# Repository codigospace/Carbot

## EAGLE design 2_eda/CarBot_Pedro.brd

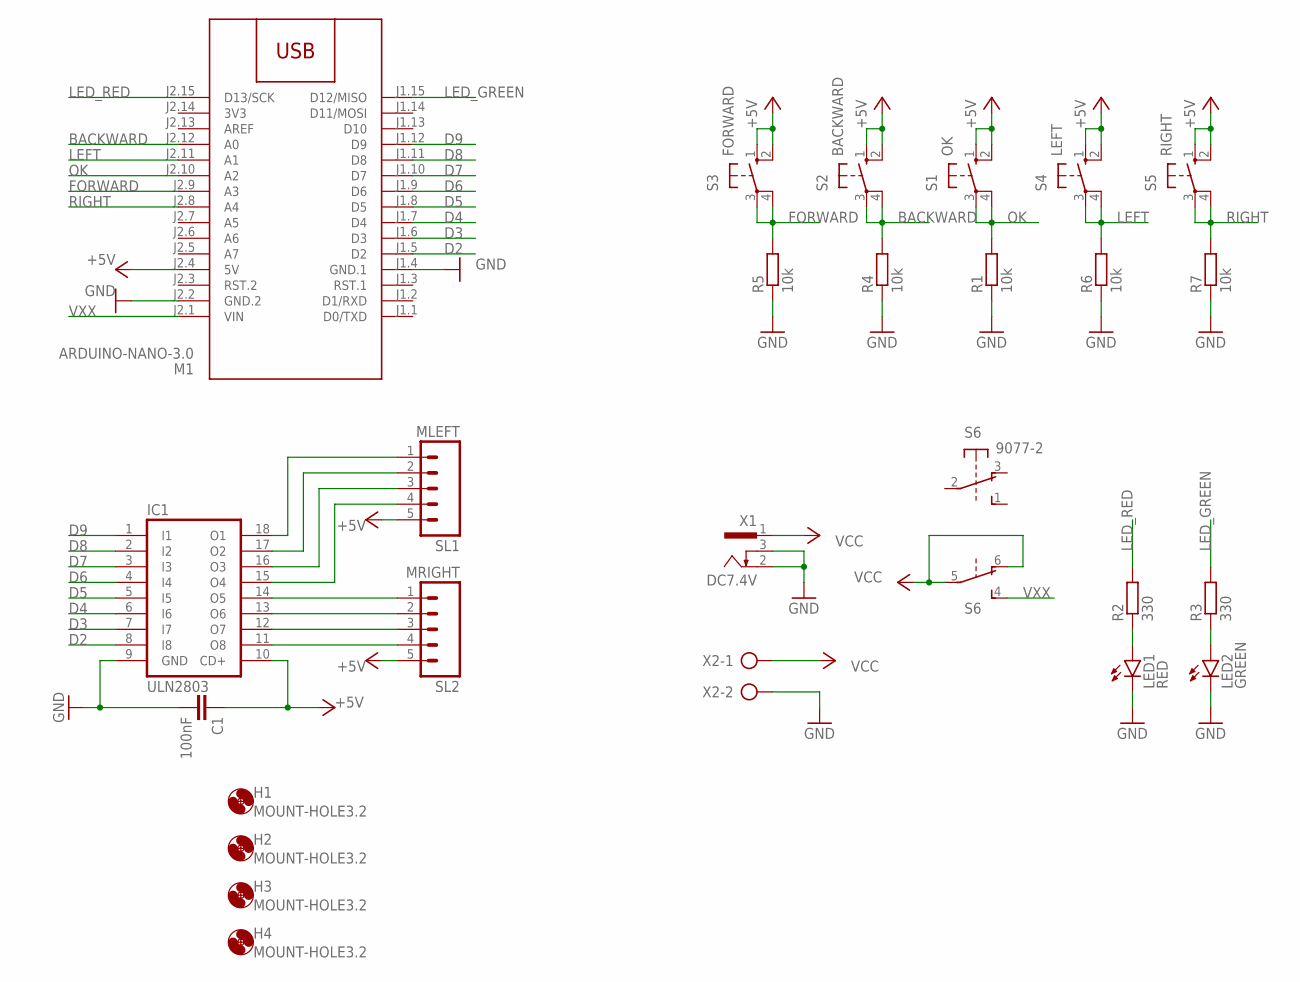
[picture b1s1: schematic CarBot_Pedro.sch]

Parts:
C1: 100nF; C025-030X050
H1, H2, H3, H4: MOUNT-HOLE3.2; 3,2
IC1: ULN2803; DIL18
LED1: RED; LED3MM
LED2: GREEN; LED3MM
M1: ARDUINO-NANO-3.0
R1, R4, R5, R6, R7: 10k; 0207/7
R2, R3: 330; 0207/7
S1: OK; B3F-40XX
S2: BACKWARD; B3F-40XX
S3: FORWARD; B3F-40XX
S4: LEFT; B3F-40XX
S5: RIGHT; B3F-40XX
S6: 9077-2
SL1: MLEFT; 05P
SL2: MRIGHT; 05P
X1: DC7.4V; 733980-62
X2: AK500/2-H

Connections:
3V3: M1.J2.14 (3V3)
+5V: C1.1, IC1.10 (CD+), M1.J2.4 (5V), S1.1 (S), S1.2 (S1), S2.1 (S), S2.2 (S1), S3.1 (S), S3.2 (S1), S4.1 (S), S4.2 (S1), S5.1 (S), S5.2 (S1), SL1.5, SL2.5
BACKWARD: M1.J2.12 (A0), R4.2, S2.3, S2.4 (P1)
D2: IC1.8 (I8), M1.J1.5 (D2)
D3: IC1.7 (I7), M1.J1.6 (D3)
D4: IC1.6 (I6), M1.J1.7 (D4)
D5: IC1.5 (I5), M1.J1.8 (D5)
D6: IC1.4 (I4), M1.J1.9 (D6)
D7: IC1.3 (I3), M1.J1.10 (D7)
D8: IC1.2 (I2), M1.J1.11 (D8)
D9: IC1.1 (I1), M1.J1.12 (D9)
FORWARD: M1.J2.9 (A3), R5.2, S3.3, S3.4 (P1)
GND: C1.2, IC1.9 (GND), LED1.K (C), LED2.K (C), M1.J1.4 (GND.1), M1.J2.2 (GND.2), R1.1, R4.1, R5.1, R6.1, R7.1, X1.2, X1.3, X2.2
LED_GREEN: M1.J1.15 (D12/MISO), R3.2
LED_RED: M1.J2.15 (D13/SCK), R2.2
LEFT: M1.J2.11 (A1), R6.2, S4.3, S4.4 (P1)
unnamed: IC1.11 (O8), SL2.4
unnamed: IC1.12 (O7), SL2.3
unnamed: IC1.13 (O6), SL2.2
unnamed: IC1.14 (O5), SL2.1
unnamed: IC1.15 (O4), SL1.4
unnamed: IC1.16 (O3), SL1.3
unnamed: IC1.17 (O2), SL1.2
unnamed: IC1.18 (O1), SL1.1
unnamed: LED1.A, R2.1
unnamed: LED2.A, R3.1
OK: M1.J2.10 (A2), R1.2, S1.3, S1.4 (P1)
RIGHT: M1.J2.8 (A4), R7.2, S5.3, S5.4 (P1)
VCC: S6.5, S6.6 (O), X1.1, X2.1
VXX: M1.J2.1 (VIN), S6.4 (S)

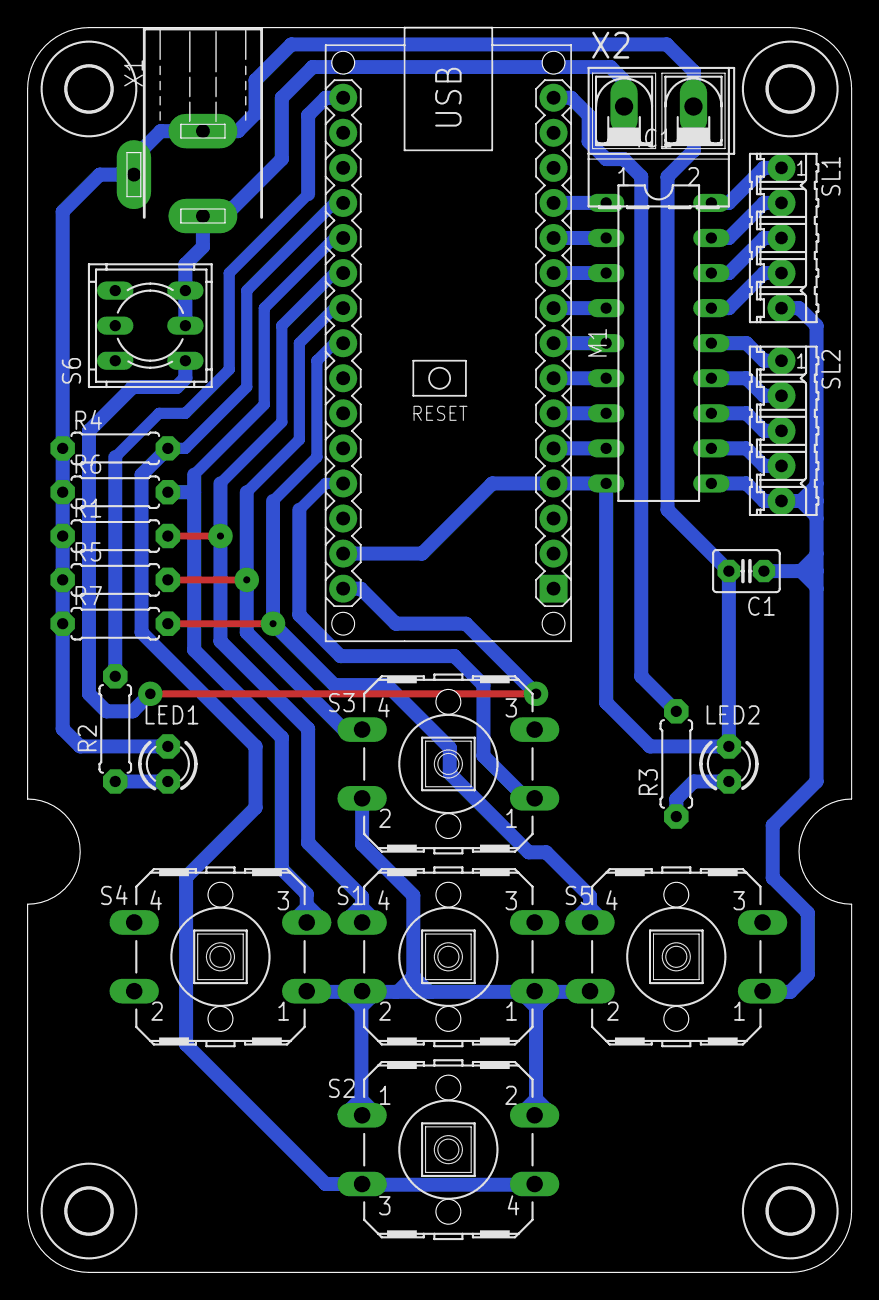
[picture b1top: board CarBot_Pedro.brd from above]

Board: 2 copper layers, 59.7 x 90.2 mm, 26 parts (0 on the bottom side), 29 nets.

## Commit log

2024-12-31 1er commit
2024-12-31 programming
2024-12-31 3D and Electronic

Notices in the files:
parts and their libraries:
diy-modules_ms: Released under the Creative Commons Attribution 4.0 International License: http://creativecommons.org/licenses/by/4.0
